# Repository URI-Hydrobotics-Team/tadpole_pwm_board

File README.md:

# tadpole_pwm_board
this is a pwm IO extender board for tadpole to allow it to control its 8 thrusters via i2c, there will also be a watchdog microcontroller that will disable PWM output if it does not receive an OK signal from the main computer at some interval.

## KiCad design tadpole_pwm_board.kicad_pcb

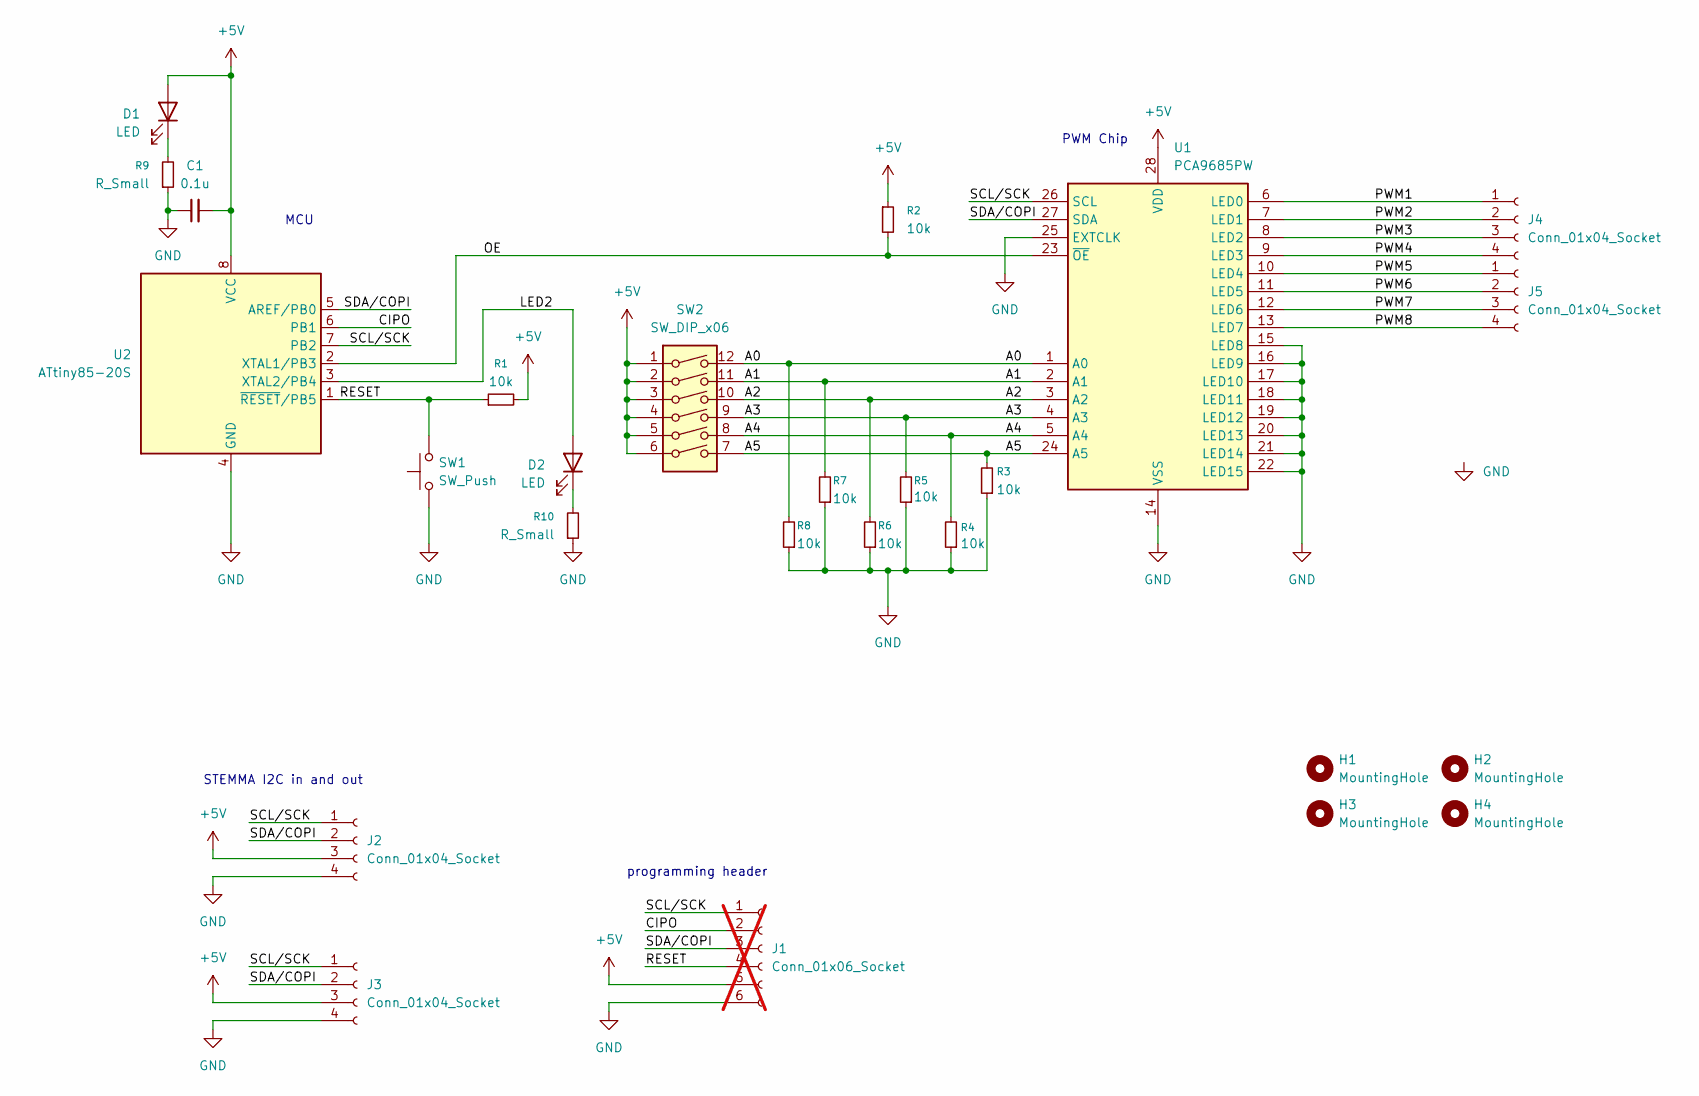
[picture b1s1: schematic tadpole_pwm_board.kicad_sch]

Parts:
C1: 0.1u; C_0805_2012Metric
D1, D2: LED; LED_0805_2012Metric
H1, H2, H3, H4: MountingHole; MountingHole_3.2mm_M3
J1: Conn_01x06_Socket; PinHeader_1x06_P2.54mm_Vertical; not fitted
J2, J3: Conn_01x04_Socket; JST_PH_S4B-PH-K_1x04_P2.00mm_Horizontal
J4, J5: Conn_01x04_Socket; JST_XH_S4B-XH-A_1x04_P2.50mm_Horizontal
R1, R2, R3, R4, R5, R6, R7, R8: 10k; R_0805_2012Metric
R9, R10: R_Small; R_0805_2012Metric
SW1: SW_Push; SW_Tactile_SPST_NO_Straight_CK_PTS636Sx25SMTRLFS
SW2: SW_DIP_x06; SW_DIP_SPSTx06_Slide_6.7x16.8mm_W8.61mm_P2.54mm_LowProfile
U1: PCA9685PW; TSSOP-28_4.4x9.7mm_P0.65mm
U2: ATtiny85-20S; SOIC-8_5.3x5.3mm_P1.27mm

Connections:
+5V: C1.2, D1.2 (A), J1.5, J2.3, J3.3, R1.2, R2.1, SW2.1, SW2.2, SW2.3, SW2.4, SW2.5, SW2.6, U1.28 (VDD), U2.8 (VCC)
/A0: R8.2, SW2.12, U1.1 (A0)
/A1: R7.2, SW2.11, U1.2 (A1)
/A2: R6.2, SW2.10, U1.3 (A2)
/A3: R5.2, SW2.9, U1.4 (A3)
/A4: R4.2, SW2.8, U1.5 (A4)
/A5: R3.2, SW2.7, U1.24 (A5)
/CIPO: J1.2, U2.6 (PB1)
/LED2: D2.2 (A), U2.3 (XTAL2/PB4)
/OE: R2.2, U1.23 (~OE), U2.2 (XTAL1/PB3)
/PWM1: J4.1, U1.6 (LED0)
/PWM2: J4.2, U1.7 (LED1)
/PWM3: J4.3, U1.8 (LED2)
/PWM4: J4.4, U1.9 (LED3)
/PWM5: J5.1, U1.10 (LED4)
/PWM6: J5.2, U1.11 (LED5)
/PWM7: J5.3, U1.12 (LED6)
/PWM8: J5.4, U1.13 (LED7)
/RESET: J1.4, R1.1, SW1.2, U2.1 (~RESET/PB5)
/SCL/SCK: J1.1, J2.1, J3.1, U1.26 (SCL), U2.7 (PB2)
/SDA/COPI: J1.3, J2.2, J3.2, U1.27 (SDA), U2.5 (AREF/PB0)
GND: C1.1, J1.6, J2.4, J3.4, R3.1, R4.1, R5.1, R6.1, R7.1, R8.1, R9.1, R10.1, SW1.1, U1.14 (VSS), U1.15 (LED8), U1.16 (LED9), U1.17 (LED10), U1.18 (LED11), U1.19 (LED12), U1.20 (LED13), U1.21 (LED14), U1.22 (LED15), U1.25 (EXTCLK), U2.4 (GND)
unnamed: D1.1 (K), R9.2
unnamed: D2.1 (K), R10.2

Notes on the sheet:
PWM Chip
programming header
STEMMA I2C in and out
MCU

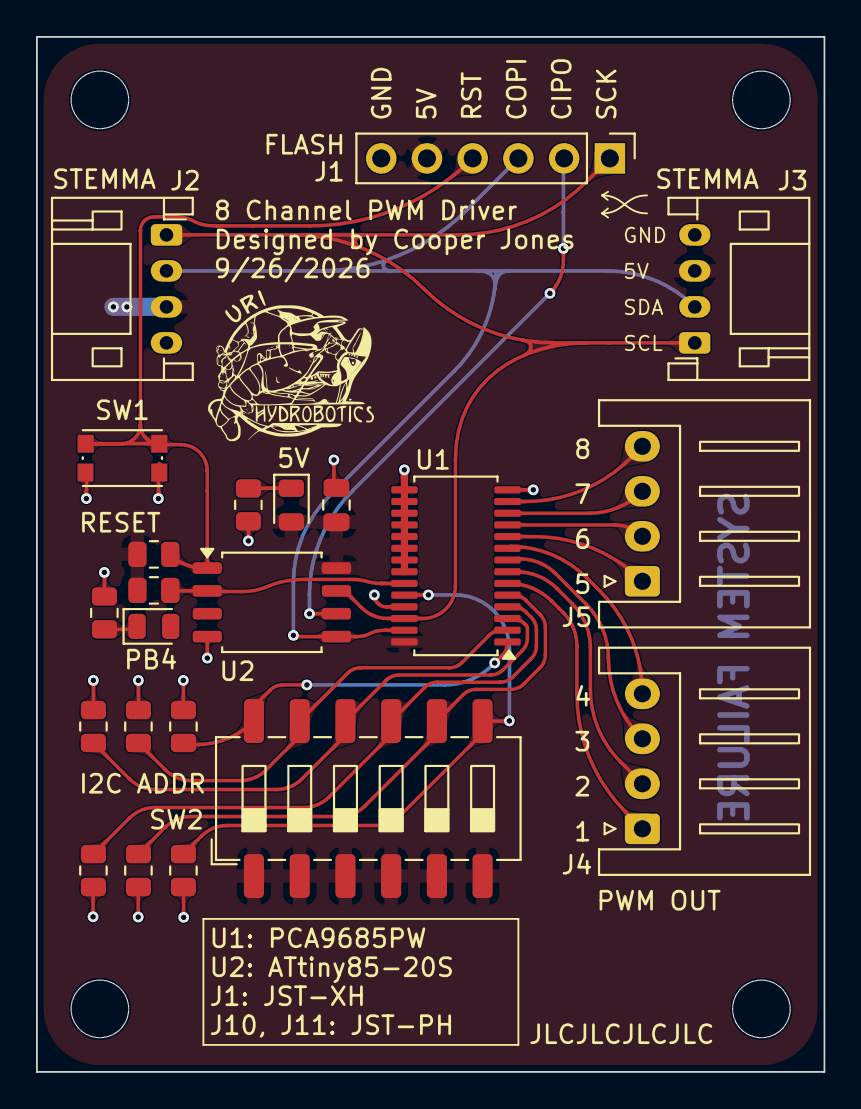
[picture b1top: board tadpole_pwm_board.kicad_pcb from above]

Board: 2 copper layers, 43.8 x 57.5 mm, 26 parts (0 on the bottom side), 24 nets.

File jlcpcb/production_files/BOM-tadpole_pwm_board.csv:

Comment,Designator,Footprint,LCSC,Quantity
10k,R2,R_0805_2012Metric,,1
10k,R4,R_0805_2012Metric,,1
ATtiny85-20S,U2,SOIC-8_5.3x5.3mm_P1.27mm,,1
Conn_01x04_Socket,J10,JST_PH_S4B-PH-K_1x04_P2.00mm_Horizontal,,1
10k,R6,R_0805_2012Metric,,1
10k,R8,R_0805_2012Metric,,1
SW_Push,SW1,SW_Push_1P1T_NO_CK_KMR2,,1
Conn_01x04_Socket,J11,JST_PH_S4B-PH-K_1x04_P2.00mm_Horizontal,,1
LED,D1,LED_0805_2012Metric,,1
10k,R1,R_0805_2012Metric,,1
10k,R7,R_0805_2012Metric,,1
10k,R3,R_0805_2012Metric,,1
10k,R5,R_0805_2012Metric,,1
0.1u,C1,C_0805_2012Metric,,1
PCA9685PW,U1,TSSOP-28_4.4x9.7mm_P0.65mm,,1
R_Small,R9,R_0805_2012Metric,,1
Conn_01x10_Socket,J1,JST_XH_S10B-XH-A_1x10_P2.50mm_Horizontal,,1
SW_DIP_x06,SW2,SW_DIP_SPSTx06_Slide_6.7x16.8mm_W8.61mm_P2.54mm_LowProfile,,1
R_Small,R10,R_0805_2012Metric,,1
LED,D2,LED_0805_2012Metric,,1

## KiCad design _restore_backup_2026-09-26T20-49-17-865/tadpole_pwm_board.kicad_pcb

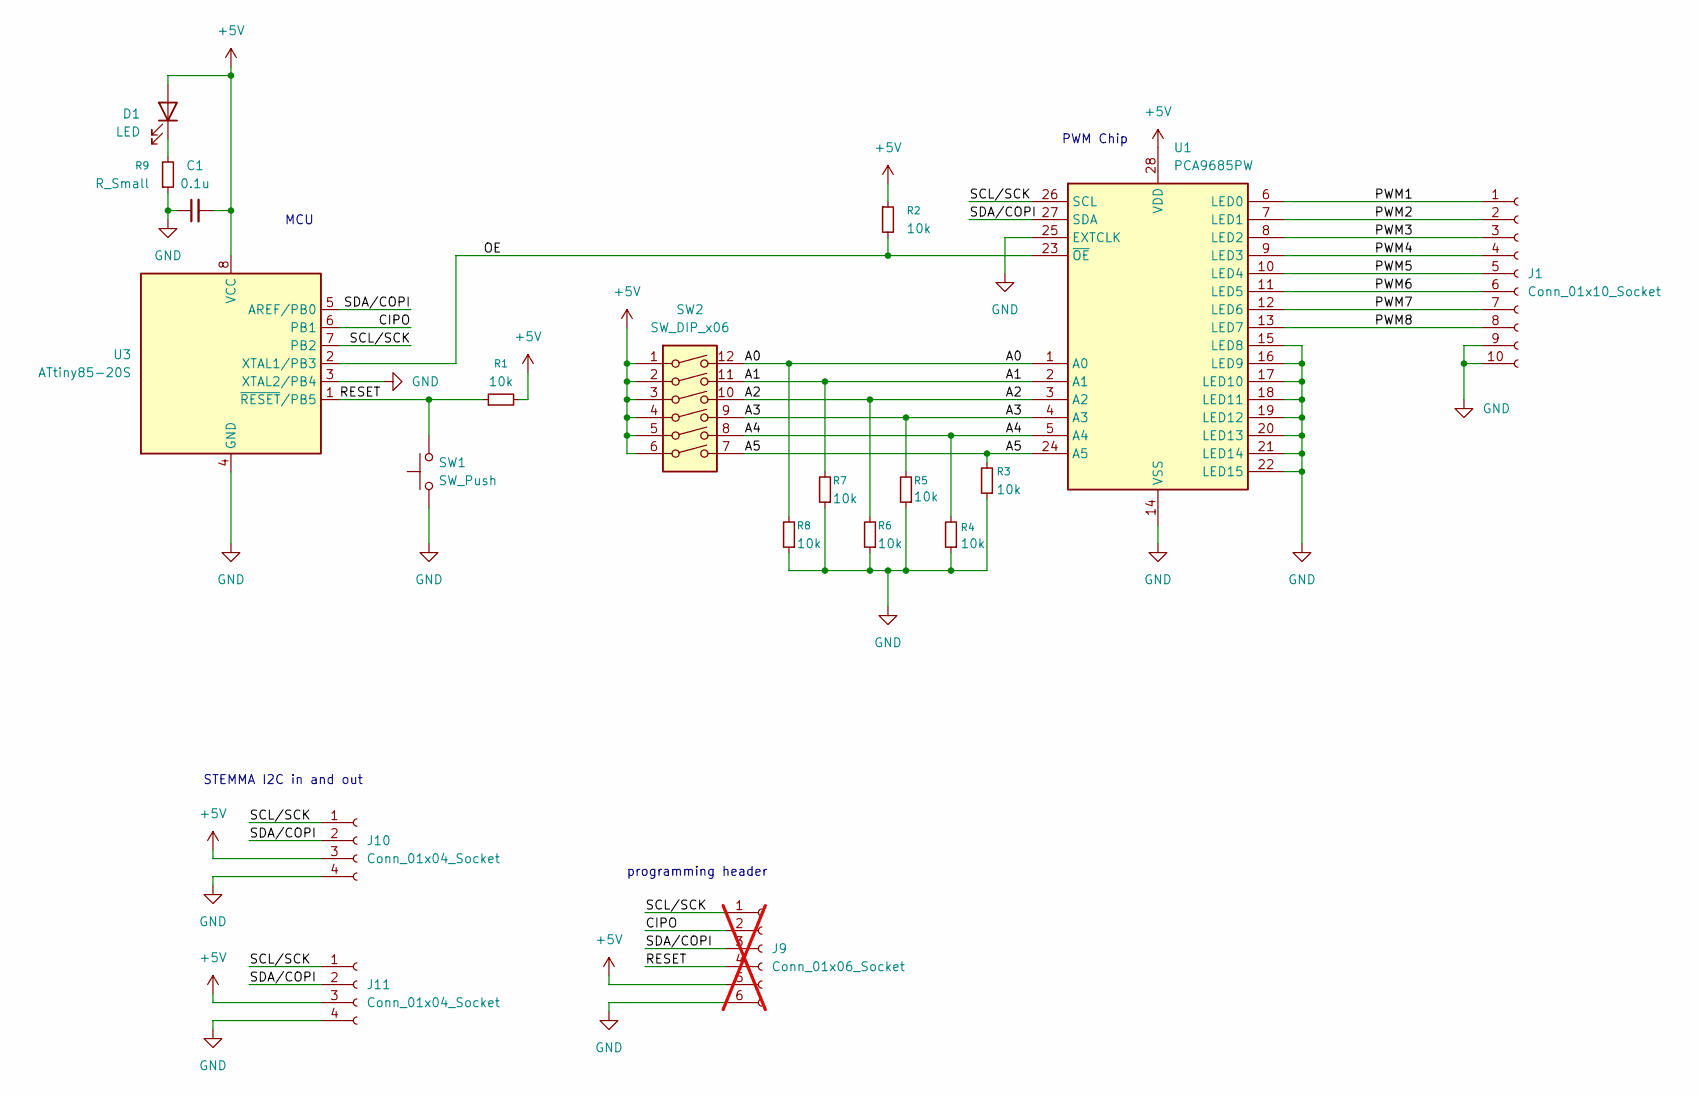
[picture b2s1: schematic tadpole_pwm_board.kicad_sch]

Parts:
C1: 0.1u; C_0805_2012Metric
D1: LED; LED_0805_2012Metric
J1: Conn_01x10_Socket; JST_XH_S10B-XH-A_1x10_P2.50mm_Horizontal
J9: Conn_01x06_Socket; PinHeader_1x06_P2.54mm_Vertical; not fitted
J10, J11: Conn_01x04_Socket; JST_PH_S4B-PH-K_1x04_P2.00mm_Horizontal
R1, R2, R3, R4, R5, R6, R7, R8: 10k; R_0805_2012Metric
R9: R_Small; R_0805_2012Metric
SW1: SW_Push; SW_SPST_SKQG_WithoutStem
SW2: SW_DIP_x06; SW_DIP_SPSTx06_Slide_6.7x16.8mm_W8.61mm_P2.54mm_LowProfile
U1: PCA9685PW; TSSOP-28_4.4x9.7mm_P0.65mm
U3: ATtiny85-20S; SOIC-8_5.3x5.3mm_P1.27mm

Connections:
+5V: C1.2, D1.2 (A), J9.5, J10.3, J11.3, R1.2, R2.1, SW2.1, SW2.2, SW2.3, SW2.4, SW2.5, SW2.6, U1.28 (VDD), U3.8 (VCC)
/A0: R8.2, SW2.12, U1.1 (A0)
/A1: R7.2, SW2.11, U1.2 (A1)
/A2: R6.2, SW2.10, U1.3 (A2)
/A3: R5.2, SW2.9, U1.4 (A3)
/A4: R4.2, SW2.8, U1.5 (A4)
/A5: R3.2, SW2.7, U1.24 (A5)
/CIPO: J9.2, U3.6 (PB1)
/OE: R2.2, U1.23 (~OE), U3.2 (XTAL1/PB3)
/PWM1: J1.1, U1.6 (LED0)
/PWM2: J1.2, U1.7 (LED1)
/PWM3: J1.3, U1.8 (LED2)
/PWM4: J1.4, U1.9 (LED3)
/PWM5: J1.5, U1.10 (LED4)
/PWM6: J1.6, U1.11 (LED5)
/PWM7: J1.7, U1.12 (LED6)
/PWM8: J1.8, U1.13 (LED7)
/RESET: J9.4, R1.1, SW1.2, U3.1 (~RESET/PB5)
/SCL/SCK: J9.1, J10.1, J11.1, U1.26 (SCL), U3.7 (PB2)
/SDA/COPI: J9.3, J10.2, J11.2, U1.27 (SDA), U3.5 (AREF/PB0)
GND: C1.1, J1.9, J1.10, J9.6, J10.4, J11.4, R3.1, R4.1, R5.1, R6.1, R7.1, R8.1, R9.1, SW1.1, U1.14 (VSS), U1.15 (LED8), U1.16 (LED9), U1.17 (LED10), U1.18 (LED11), U1.19 (LED12), U1.20 (LED13), U1.21 (LED14), U1.22 (LED15), U1.25 (EXTCLK), U3.3 (XTAL2/PB4), U3.4 (GND)
unnamed: D1.1 (K), R9.2

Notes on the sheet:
PWM Chip
programming header
STEMMA I2C in and out
MCU

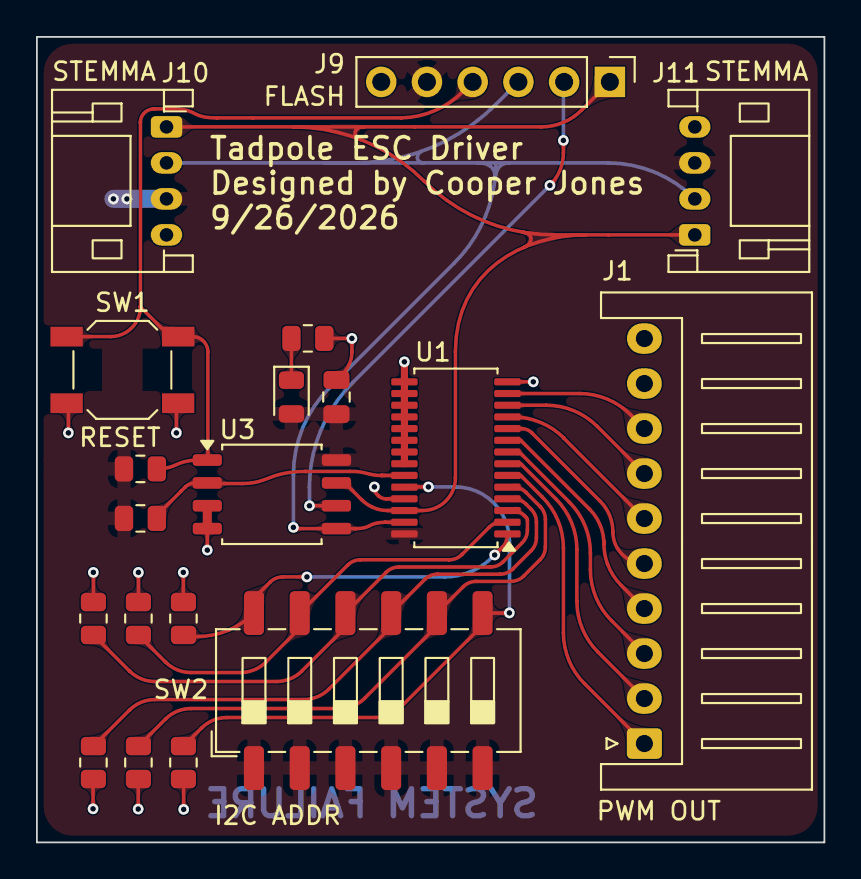
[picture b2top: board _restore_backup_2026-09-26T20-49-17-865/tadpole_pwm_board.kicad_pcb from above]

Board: 2 copper layers, 43.8 x 44.8 mm, 19 parts (0 on the bottom side), 22 nets.
